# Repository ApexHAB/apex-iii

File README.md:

# Apex III
## A next generation high altitude balloon project by Sutton Grammar School

## Useful links

* [Homepage](http://www.apexhab.org) - http://www.apexhab.org
* [Apex III Homepage](http://www.apexhab.org/apex-iii/) - http://www.apexhab.org/apex-iii/
* [Contact](mailto:team@apexhab.org) - team@apexhab.org
* [Twitter](http://twitter.com/apexhab) - http://twitter.com/apexhab

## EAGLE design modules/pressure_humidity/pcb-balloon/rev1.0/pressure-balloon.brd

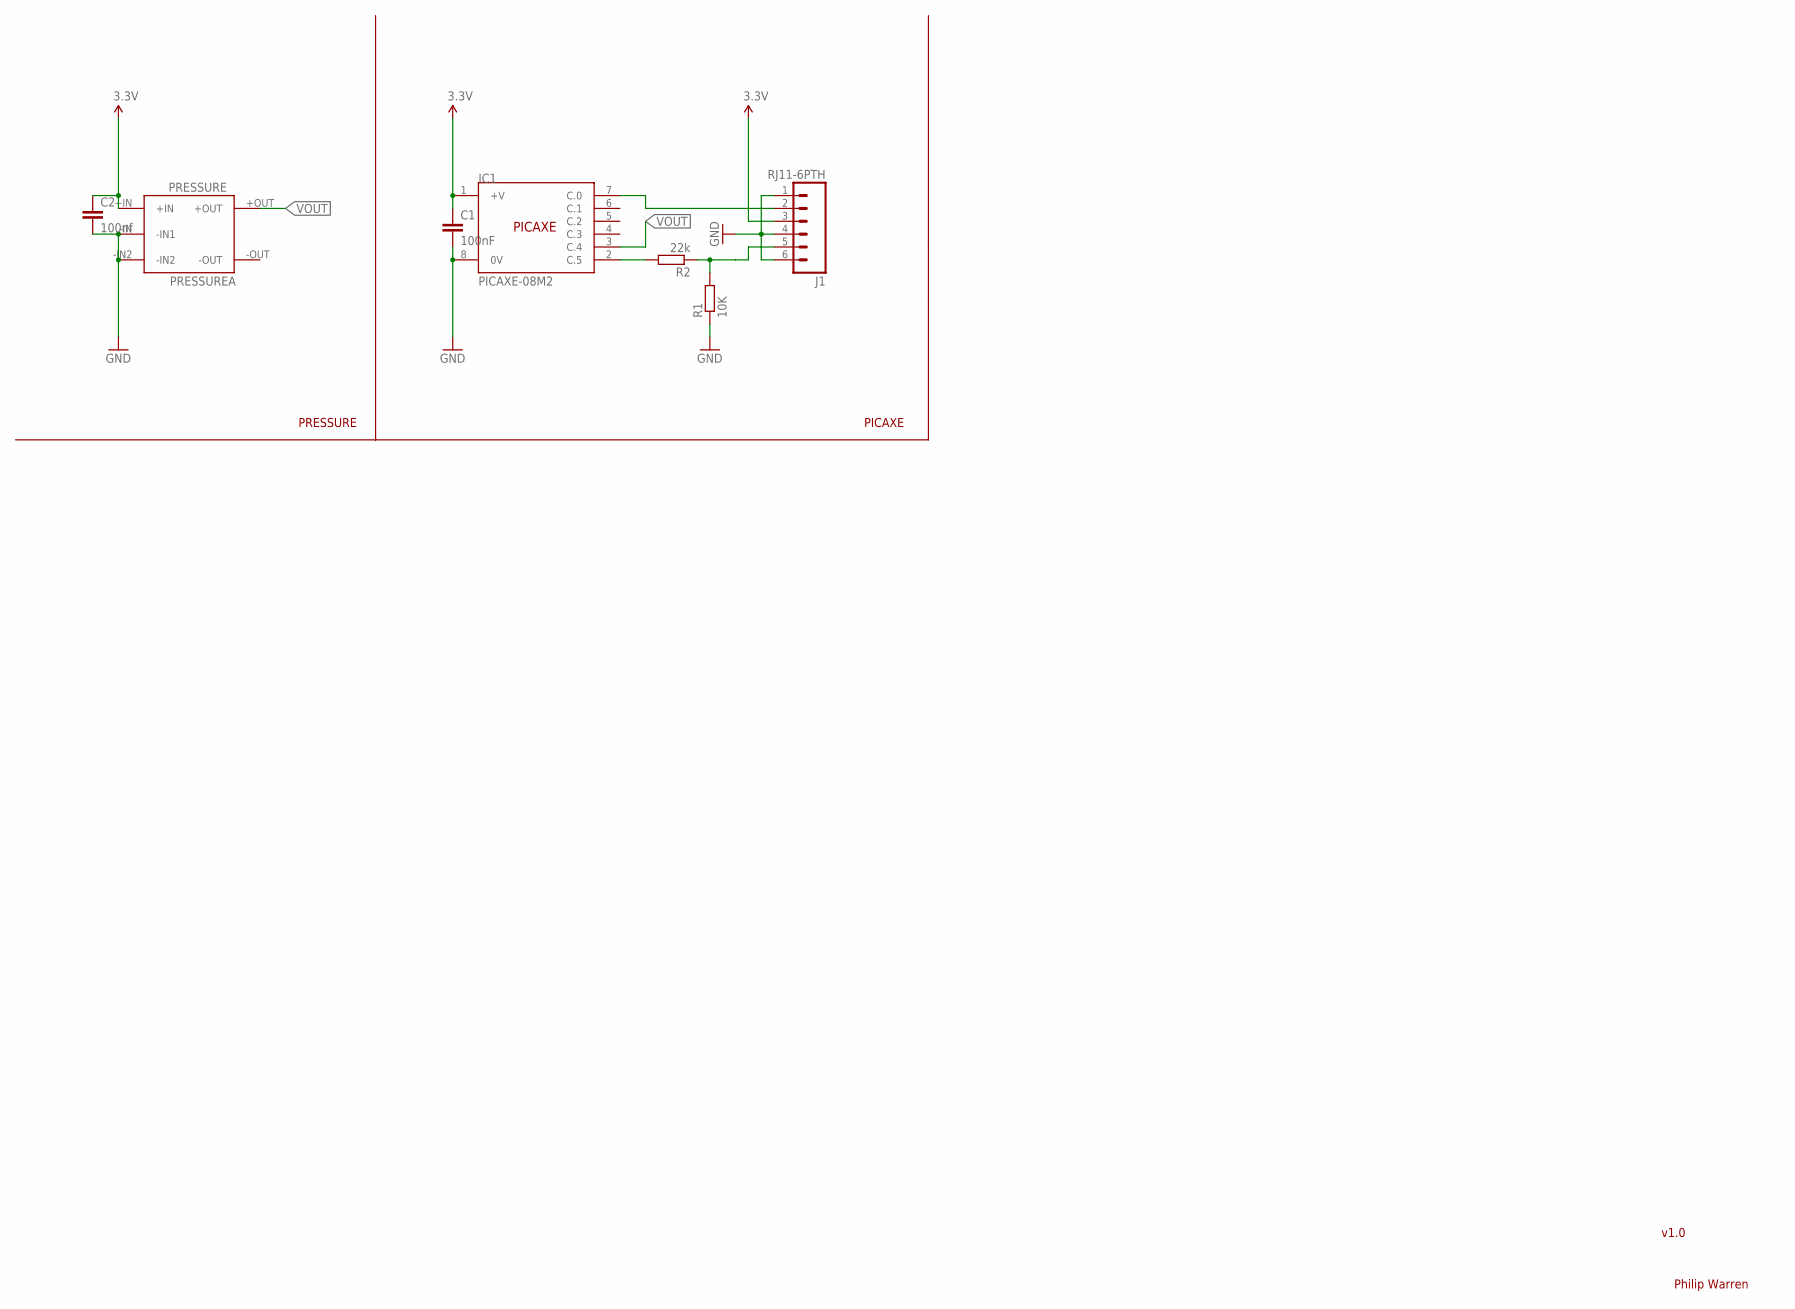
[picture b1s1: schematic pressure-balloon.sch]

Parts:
C1: 100nF; 0805
C2: 100nf; 0805
IC1: PICAXE-08M2; SOIC8
J1: RJ11-6PTH; RJ11-6
PRESSURE: PRESSUREA; PRESSURE
R1: 10K; R0805
R2: 22k; R0805

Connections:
3.3V: C1.1, C2.1, IC1.1 (+V), J1.3, PRESSURE.+IN
GND: C1.2, C2.2, IC1.8 (0V), J1.1, J1.4, J1.6, PRESSURE.-IN (-IN1), PRESSURE.-IN2, R1.1
unnamed: IC1.7 (C.0), J1.2
unnamed: J1.5, R1.2, R2.1
unnamed: IC1.2 (C.5), R2.2
VOUT: IC1.3 (C.4), PRESSURE.+OUT

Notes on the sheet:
PICAXE
PRESSURE
Philip Warren
v1.0

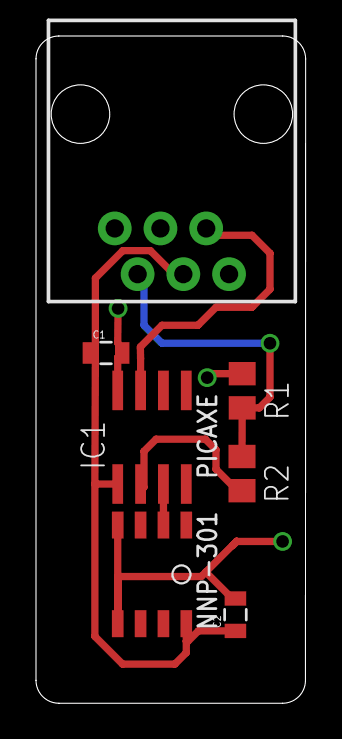
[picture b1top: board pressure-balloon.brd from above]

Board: 2 copper layers, 15.0 x 37.1 mm, 7 parts (0 on the bottom side), 6 nets.

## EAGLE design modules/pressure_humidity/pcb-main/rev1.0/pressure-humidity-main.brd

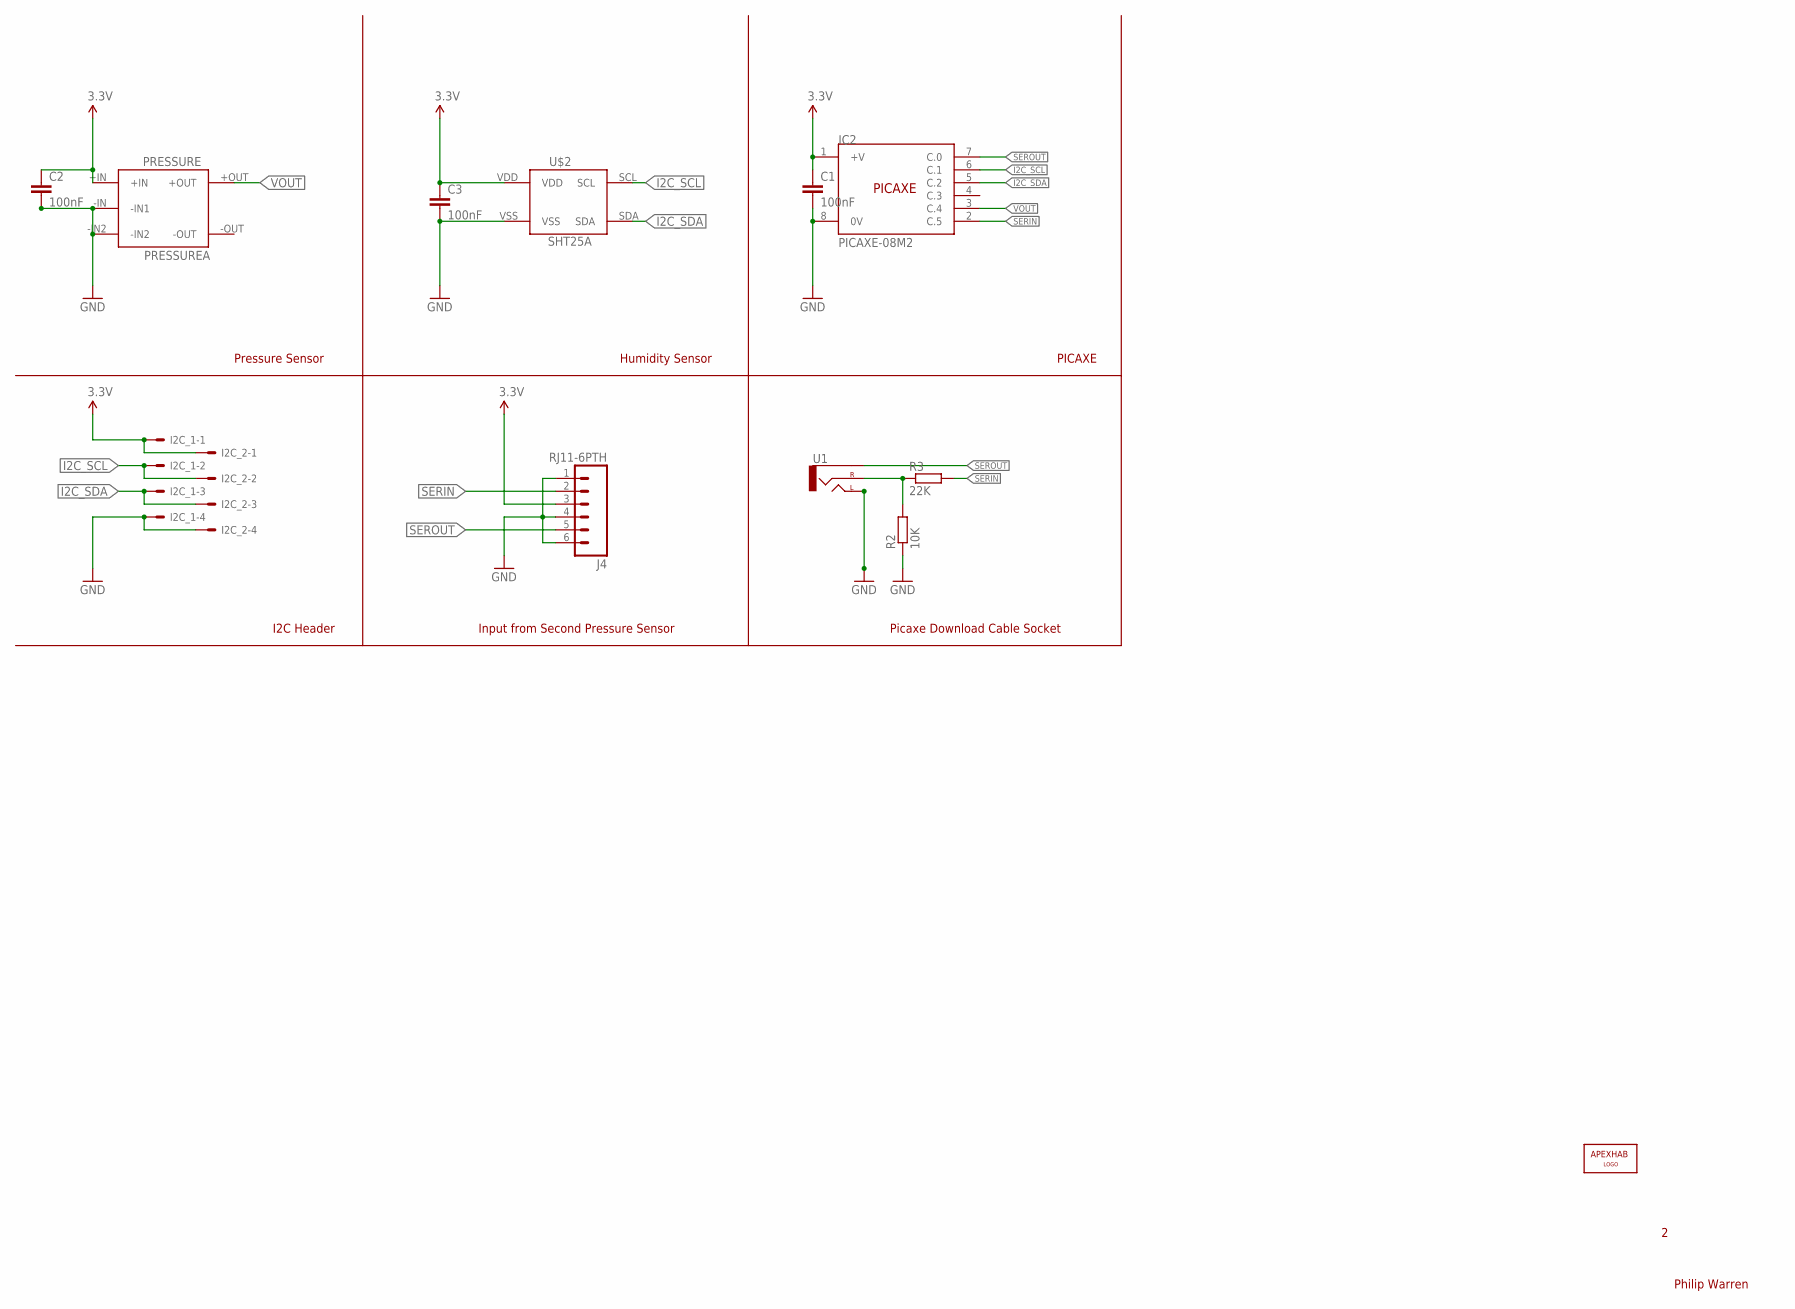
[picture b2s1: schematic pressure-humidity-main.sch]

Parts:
C1, C2, C3: 100nF; 0805
I2C_1, I2C_2: 22-27-2041-04; 6410-04
IC2: PICAXE-08M2; SOIC8
J4: RJ11-6PTH; RJ11-6
JP1: APEXHAB-LOGO_APEXHAB-SMALL; APEXHAB-LOGO-SMALL
PRESSURE: PRESSUREA; PRESSURE
R2: 10K; R0805
R3: 22K; R0805
U1: AUDIO-JACKPTH; AUDIO-JACK
U$2: SHT25A; SHT25

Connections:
3.3V: C1.1, C2.1, C3.1, I2C_1.1, I2C_2.1, IC2.1 (+V), J4.3, PRESSURE.+IN, U$2.VDD
GND: C1.2, C2.2, C3.2, I2C_1.4, I2C_2.4, IC2.8 (0V), J4.1, J4.4, J4.6, PRESSURE.-IN (-IN1), PRESSURE.-IN2, R2.1, U1.TIP (LEFT), U$2.VSS
I2C_SCL: I2C_1.2, I2C_2.2, IC2.6 (C.1), U$2.SCL
I2C_SDA: I2C_1.3, I2C_2.3, IC2.5 (C.2), U$2.SDA
unnamed: R2.2, R3.1, U1.RING (RIGHT)
SERIN: IC2.2 (C.5), J4.2, R3.2
SEROUT: IC2.7 (C.0), J4.5, U1.SLEEVE
VOUT: IC2.3 (C.4), PRESSURE.+OUT

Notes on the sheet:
Pressure Sensor
Humidity Sensor
PICAXE
Picaxe Download Cable Socket
Input from Second Pressure Sensor
I2C Header
Philip Warren

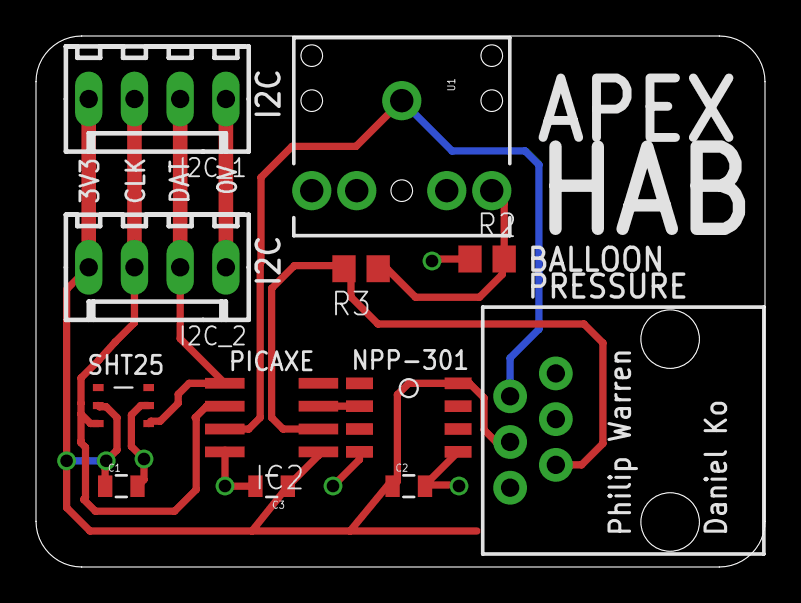
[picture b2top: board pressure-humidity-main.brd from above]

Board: 2 copper layers, 40.5 x 29.5 mm, 13 parts (1 on the bottom side), 8 nets.

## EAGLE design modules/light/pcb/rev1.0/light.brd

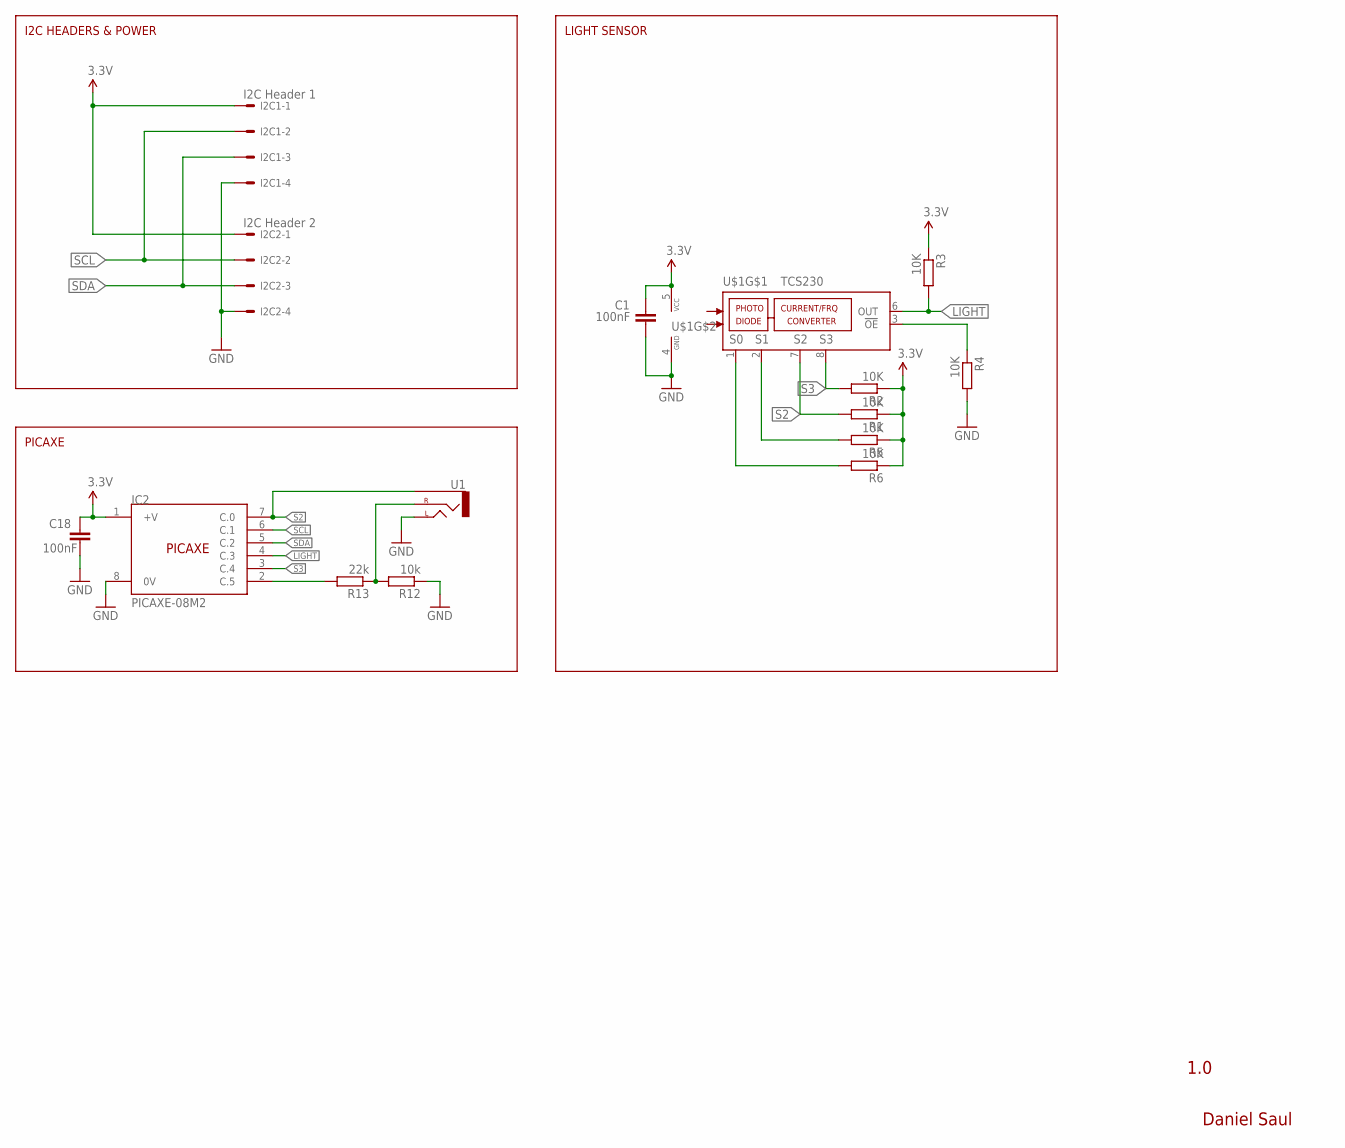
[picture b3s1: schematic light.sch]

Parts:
C1, C18: 100nF; C0805
I2C1: I2C Header 1; 6410-04
I2C2: I2C Header 2; 6410-04
IC2: PICAXE-08M2; SOIC8
R1, R2, R3, R4, R5, R6: 10K; R0805
R12: 10k; R0805
R13: 22k; R0805
U1: AUDIO-JACKPTH; AUDIO-JACK
U$1: TCS230; SOIC8

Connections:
3.3V: C1.1, C18.1, I2C1.1, I2C2.1, IC2.1 (+V), R1.1, R2.1, R3.1, R5.1, R6.1, U$1.5 (VCC)
GND: C1.2, C18.2, I2C1.4, I2C2.4, IC2.8 (0V), R4.2, R12.1, U1.TIP (LEFT), U$1.4 (GND)
LIGHT: IC2.4 (C.3), R3.2, U$1.6 (OUT)
unnamed: R5.2, U$1.2 (S1)
unnamed: R4.1, U$1.3 (!OE)
unnamed: R6.2, U$1.1 (S0)
unnamed: IC2.2 (C.5), R13.2
unnamed: R12.2, R13.1, U1.RING (RIGHT)
S2: IC2.7 (C.0), R1.2, U1.SLEEVE, U$1.7 (S2)
S3: IC2.3 (C.4), R2.2, U$1.8 (S3)
SCL: I2C1.2, I2C2.2, IC2.6 (C.1)
SDA: I2C1.3, I2C2.3, IC2.5 (C.2)

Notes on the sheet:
1.0
Daniel Saul
I2C HEADERS & POWER
PICAXE
LIGHT SENSOR

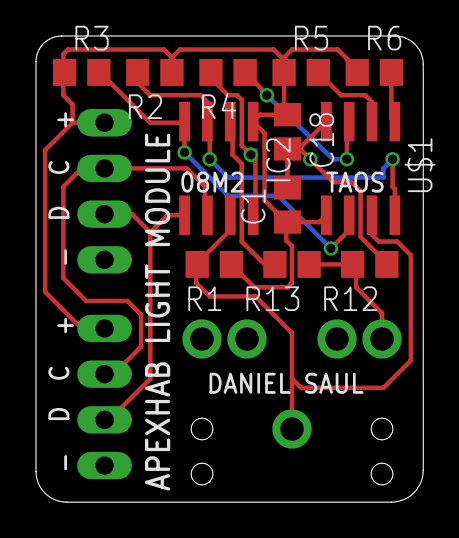
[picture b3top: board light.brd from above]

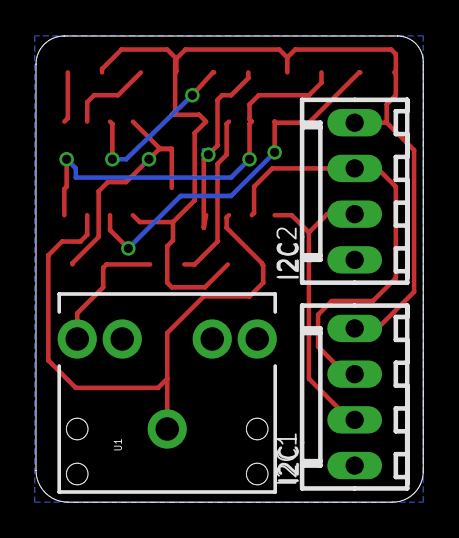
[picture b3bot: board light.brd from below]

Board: 2 copper layers, 21.5 x 25.9 mm, 15 parts (3 on the bottom side), 12 nets.

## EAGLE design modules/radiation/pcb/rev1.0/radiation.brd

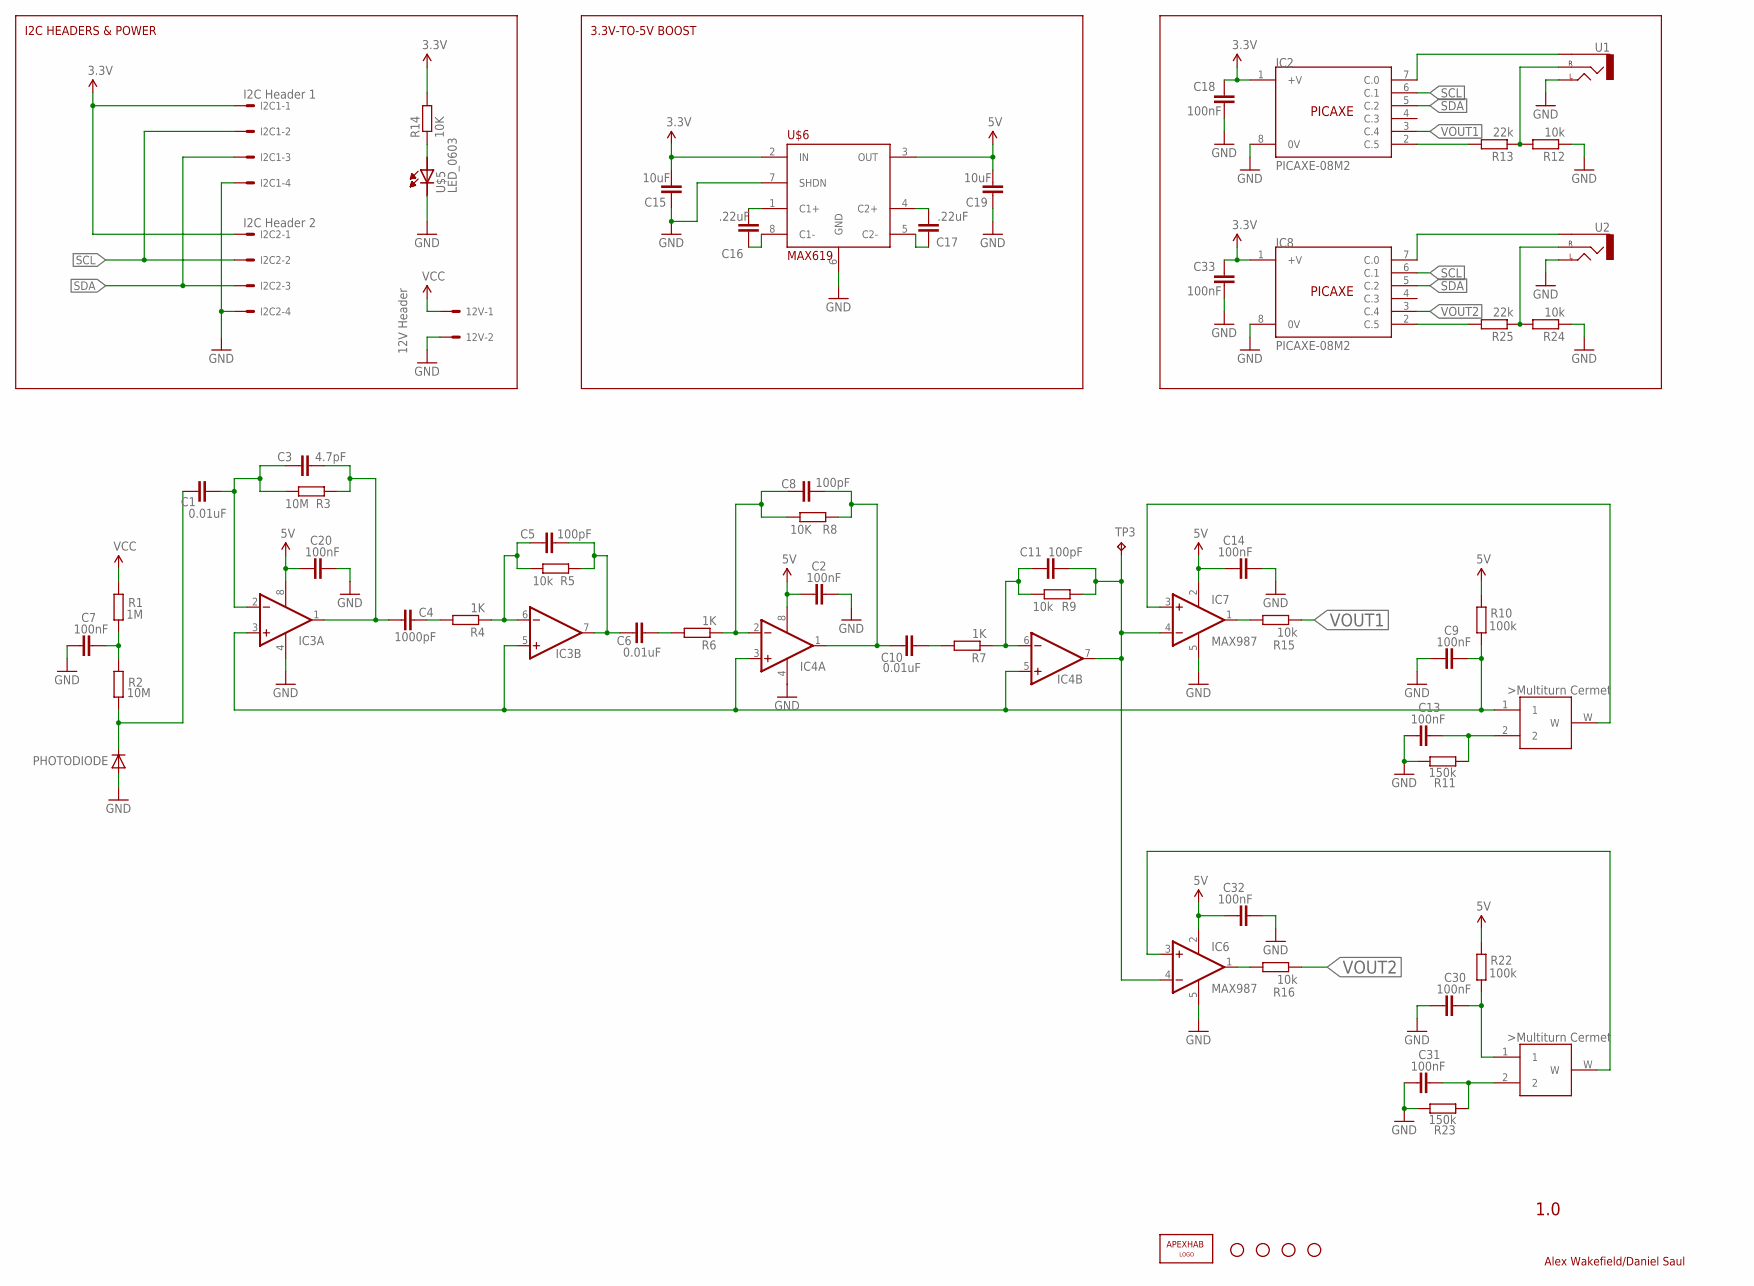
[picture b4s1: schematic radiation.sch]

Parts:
12V: 12V Header; 6410-02
C1, C6, C10: 0.01uF; C0805
C2, C7, C9, C13, C14, C18, C20, C30, C31, C32, C33: 100nF; C0805
C3: 4.7pF; C0805
C4: 1000pF; C0805
C5, C8, C11: 100pF; C0805
C15, C19: 10uF; C0805
C16, C17: .22uF; C0805
I2C1: I2C Header 1; 6410-04
I2C2: I2C Header 2; 6410-04
IC2, IC8: PICAXE-08M2; SOIC8
IC3: max4477; SO08
IC4: <AX4477; SO08
IC6, IC7: MAX987; SOT23-5
JP1: APEXHAB-LOGO_APEX; APEX-LOGO
JP2, JP3, JP4, JP5: STAND-OFF
PHOTODIODE: DIODE-D-2.5; D-2.5
R1: 1M; R0805
R2, R3: 10M; R0805
R4, R6, R7: 1K; R0805
R5, R9, R12, R15, R16, R24: 10k; R0805
R8, R14: 10K; R0805
R10, R22: 100k; R0805
R11, R23: 150k; R0805
R13, R25: 22k; R0805
TP3: TPTP10SQ; TP10SQ
U1, U2: AUDIO-JACKPTH; AUDIO-JACK
U$3, U$4: YL_SMT_11-TURN_CERMET_TRIMMER,_10K_0.25W
U$5: LED_0603; CHIPLED_0603
U$6: MAX619; SO8

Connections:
3.3V: C15.2, C18.1, C33.1, I2C1.1, I2C2.1, IC2.1 (+V), IC8.1 (+V), R14.2, U$6.2 (IN)
5V: C2.1, C14.1, C19.2, C20.1, C32.1, IC3.8 (V+), IC4.8 (V+), IC6.2 (V+), IC7.2 (V+), R10.1, R22.1, U$6.3 (OUT)
GND: 12V.2, C2.2, C7.1, C9.1, C13.1, C14.2, C15.1, C18.2, C19.1, C20.2, C30.1, C31.1, C32.2, C33.2, I2C1.4, I2C2.4, IC2.8 (0V), IC3.4 (V-), IC4.4 (V-), IC6.5 (V-), IC7.5 (V-), IC8.8 (0V), PHOTODIODE.A, R11.2, R12.1, R23.2, R24.1, U1.TIP (LEFT), U2.TIP (LEFT), U$5.C, U$6.6 (GND), U$6.7 (SHDN)
unnamed: C7.2, R1.1, R2.2
unnamed: C1.1, PHOTODIODE.C, R2.1
unnamed: C1.2, C3.1, IC3.2 (-IN), R3.2
unnamed: C4.2, R4.2
unnamed: C3.2, C4.1, IC3.1 (OUT), R3.1
unnamed: C5.1, IC3.6 (-IN), R4.1, R5.2
unnamed: C6.2, R6.2
unnamed: C5.2, C6.1, IC3.7 (OUT), R5.1
unnamed: C8.1, IC4.2 (-IN), R6.1, R8.2
unnamed: C13.2, R11.1, U$4.2
unnamed: C10.2, R7.2
unnamed: C11.1, IC4.6 (-IN), R7.1, R9.2
unnamed: IC8.7 (C.0), U2.SLEEVE
unnamed: IC7.3 (+IN), U$4.W
unnamed: C30.2, R22.2, U$3.1
unnamed: IC7.1 (OUT), R15.2
unnamed: IC2.2 (C.5), R13.2
unnamed: IC2.7 (C.0), U1.SLEEVE
unnamed: IC8.2 (C.5), R25.2
unnamed: R12.2, R13.1, U1.RING (RIGHT)
unnamed: R14.1, U$5.A
unnamed: C16.2, U$6.1 (C1+)
unnamed: C16.1, U$6.8 (C1-)
unnamed: C17.2, U$6.4 (C2+)
unnamed: C17.1, U$6.5 (C2-)
unnamed: C11.2, IC4.7 (OUT), IC6.4 (-IN), IC7.4 (-IN), R9.1, TP3.TP
unnamed: IC6.1 (OUT), R16.2
unnamed: C8.2, C10.1, IC4.1 (OUT), R8.1
unnamed: C9.2, IC3.3 (+IN), IC3.5 (+IN), IC4.3 (+IN), IC4.5 (+IN), R10.2, U$4.1
unnamed: C31.2, R23.1, U$3.2
unnamed: IC6.3 (+IN), U$3.W
unnamed: R24.2, R25.1, U2.RING (RIGHT)
SCL: I2C1.2, I2C2.2, IC2.6 (C.1), IC8.6 (C.1)
SDA: I2C1.3, I2C2.3, IC2.5 (C.2), IC8.5 (C.2)
VCC: 12V.1, R1.2
VOUT1: IC2.3 (C.4), R15.1
VOUT2: IC8.3 (C.4), R16.1

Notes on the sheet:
1.0
Alex Wakefield/Daniel Saul
I2C HEADERS & POWER
3.3V-TO-5V BOOST

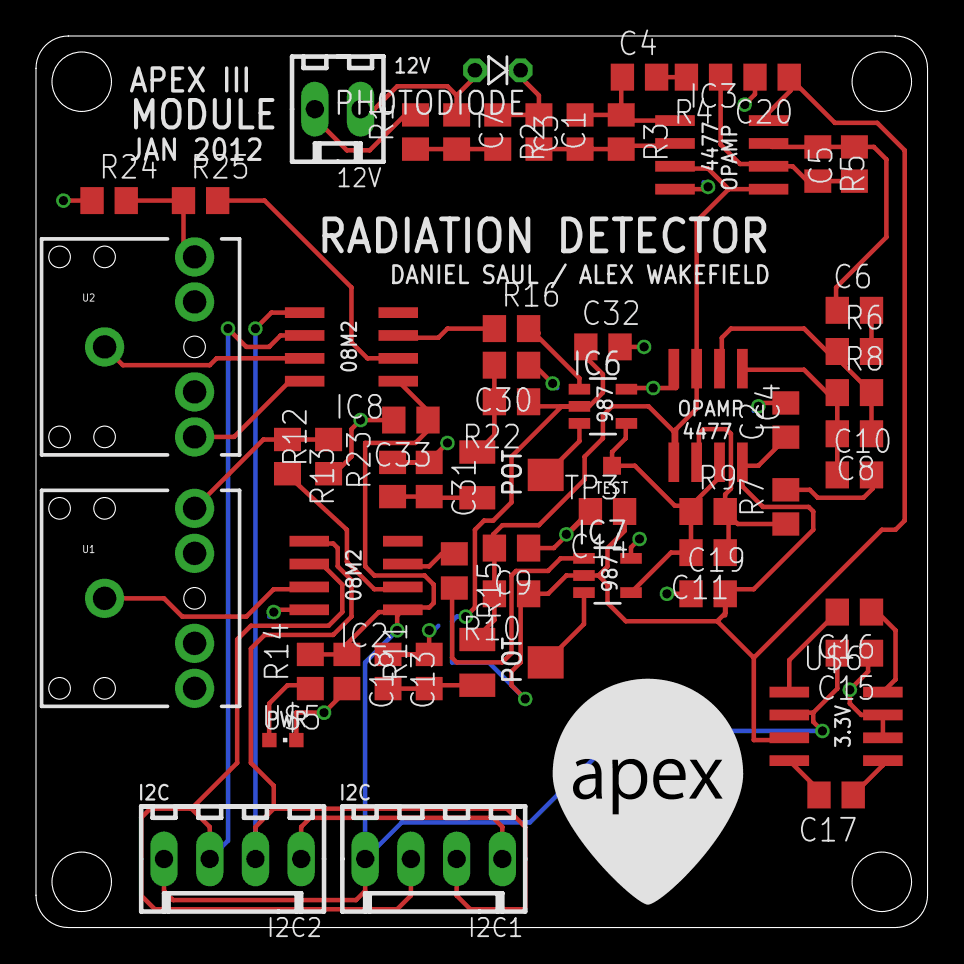
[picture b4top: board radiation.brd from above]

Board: 2 copper layers, 49.5 x 49.5 mm, 65 parts (0 on the bottom side), 40 nets.

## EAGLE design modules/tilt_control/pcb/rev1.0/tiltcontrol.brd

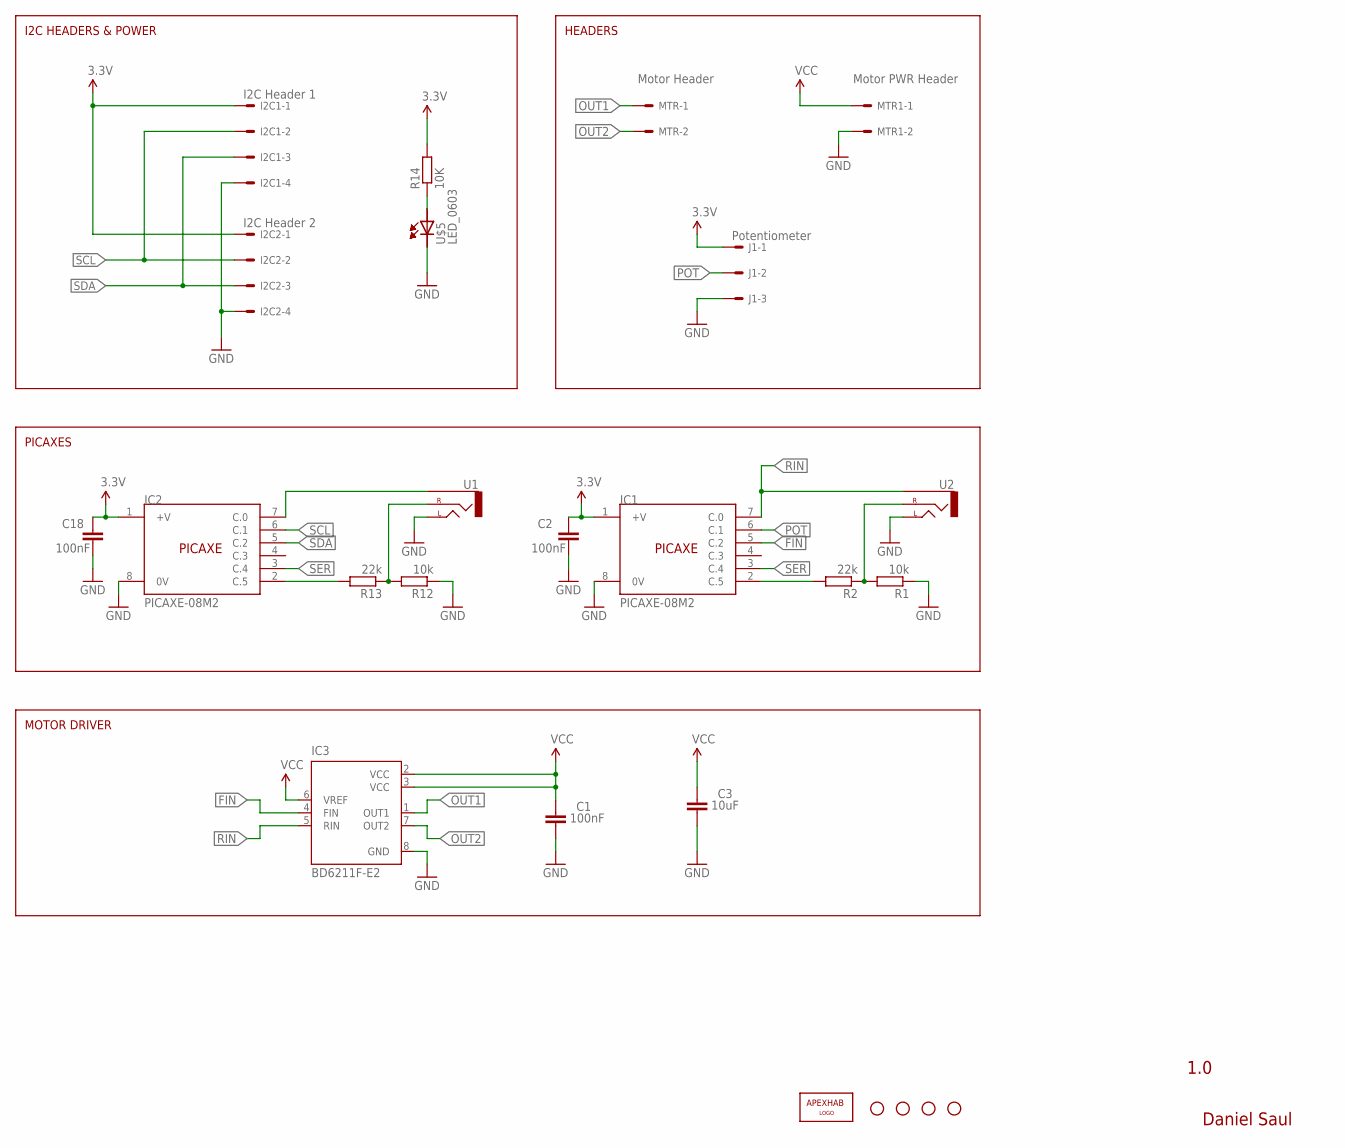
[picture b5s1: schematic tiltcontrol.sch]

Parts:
C1, C2, C18: 100nF; C0805
C3: 10uF; C0805
I2C1: I2C Header 1; 6410-04
I2C2: I2C Header 2; 6410-04
IC1, IC2: PICAXE-08M2; SOIC8
IC3: BD6211F-E2; SOP8
J1: Potentiometer; 6410-03
JP1: APEXHAB-LOGO_APEXHAB-SMALL; APEXHAB-LOGO-SMALL
JP2, JP3, JP4, JP5: STAND-OFF
MTR: Motor Header; 6410-02
MTR1: Motor PWR Header; 6410-02
R1, R12: 10k; R0805
R2, R13: 22k; R0805
R14: 10K; R0805
U1, U2: AUDIO-JACKPTH; AUDIO-JACK
U$5: LED_0603; CHIPLED_0603

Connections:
3.3V: C2.1, C18.1, I2C1.1, I2C2.1, IC1.1 (+V), IC2.1 (+V), J1.1, R14.2
FIN: IC1.5 (C.2), IC3.4 (FIN)
GND: C1.2, C2.2, C3.2, C18.2, I2C1.4, I2C2.4, IC1.8 (0V), IC2.8 (0V), IC3.8 (GND), J1.3, MTR1.2, R1.1, R12.1, U1.TIP (LEFT), U2.TIP (LEFT), U$5.C
unnamed: IC1.2 (C.5), R2.2
unnamed: R1.2, R2.1, U2.RING (RIGHT)
unnamed: IC2.2 (C.5), R13.2
unnamed: IC2.7 (C.0), U1.SLEEVE
unnamed: R12.2, R13.1, U1.RING (RIGHT)
unnamed: R14.1, U$5.A
OUT1: IC3.1 (OUT1), MTR.1
OUT2: IC3.7 (OUT2), MTR.2
POT: IC1.6 (C.1), J1.2
RIN: IC1.7 (C.0), IC3.5 (RIN), U2.SLEEVE
SCL: I2C1.2, I2C2.2, IC2.6 (C.1)
SDA: I2C1.3, I2C2.3, IC2.5 (C.2)
SER: IC1.3 (C.4), IC2.3 (C.4)
VCC: C1.1, C3.1, IC3.2 (VCC), IC3.3 (VCC), IC3.6 (VREF), MTR1.1

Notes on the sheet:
1.0
Daniel Saul
I2C HEADERS & POWER
HEADERS
PICAXES
MOTOR DRIVER

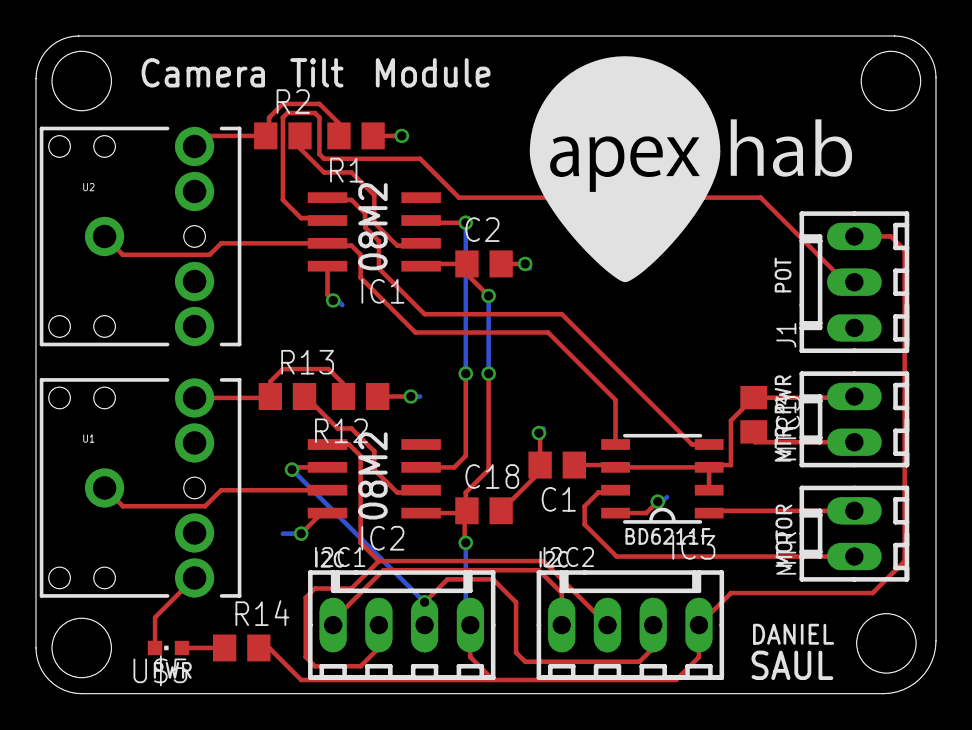
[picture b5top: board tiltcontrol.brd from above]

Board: 2 copper layers, 50.0 x 36.5 mm, 25 parts (0 on the bottom side), 17 nets.

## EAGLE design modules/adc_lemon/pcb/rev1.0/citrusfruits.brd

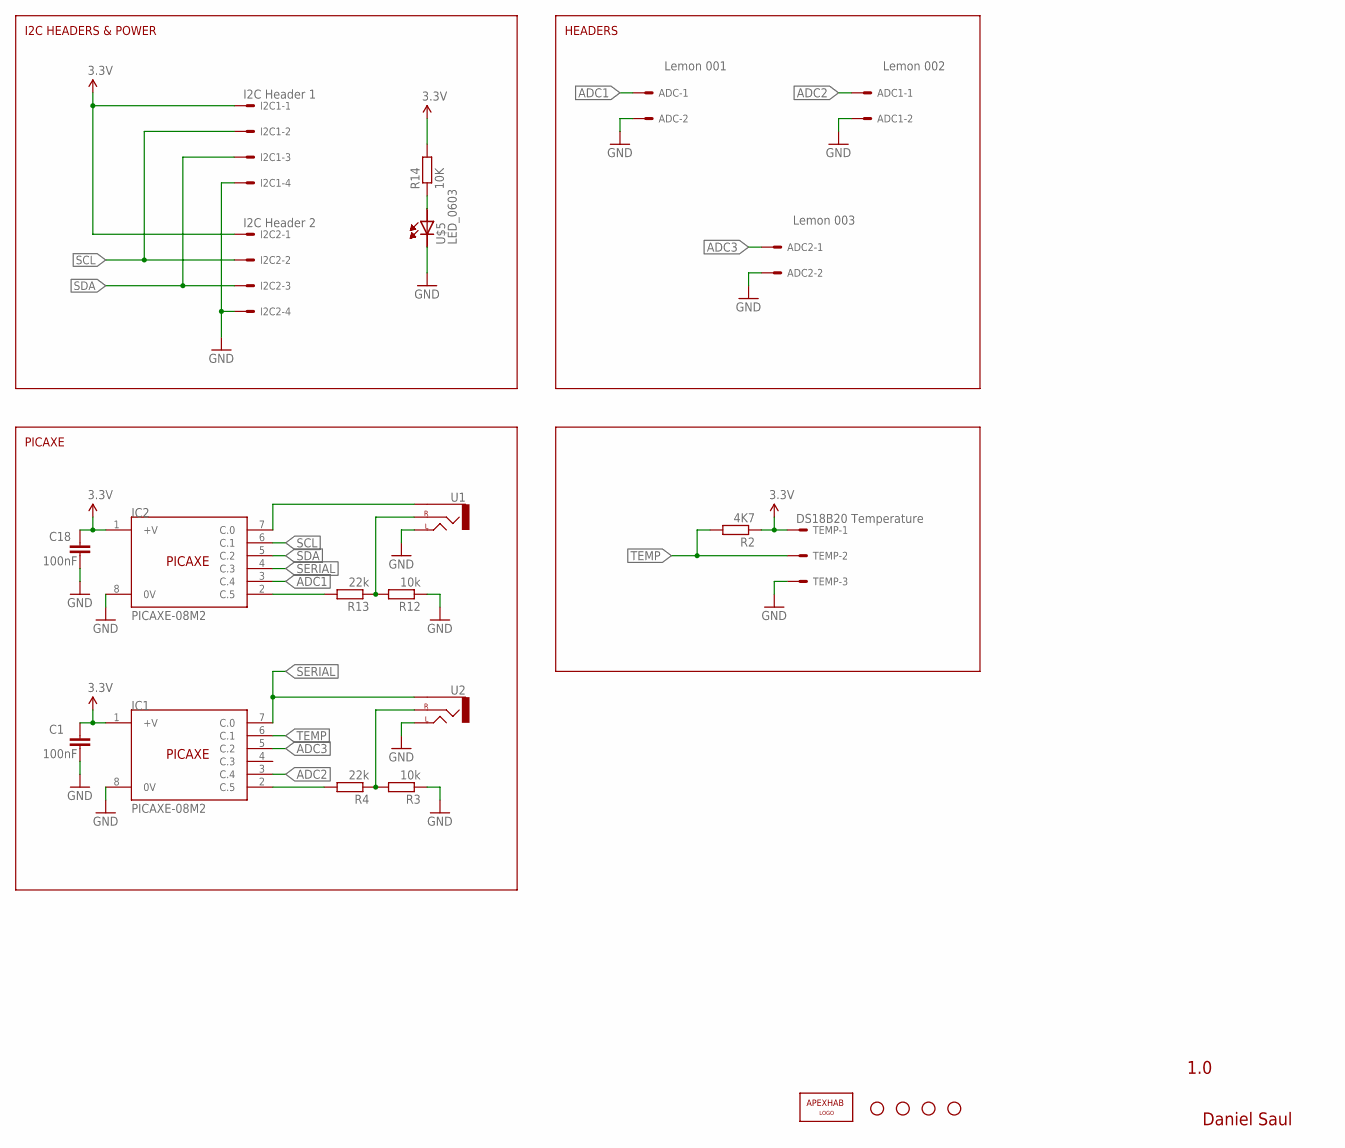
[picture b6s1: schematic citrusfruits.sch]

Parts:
ADC: Lemon 001; 6410-02
ADC1: Lemon 002; 6410-02
ADC2: Lemon 003; 6410-02
C1, C18: 100nF; C0805
I2C1: I2C Header 1; 6410-04
I2C2: I2C Header 2; 6410-04
IC1, IC2: PICAXE-08M2; SOIC8
JP1: APEXHAB-LOGO_APEXHAB-SMALL; APEXHAB-LOGO-SMALL
JP2, JP3, JP4, JP5: STAND-OFF
R2: 4K7; R0805
R3, R12: 10k; R0805
R4, R13: 22k; R0805
R14: 10K; R0805
TEMP: DS18B20 Temperature; 6410-03
U1, U2: AUDIO-JACKPTH; AUDIO-JACK
U$5: LED_0603; CHIPLED_0603

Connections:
3.3V: C1.1, C18.1, I2C1.1, I2C2.1, IC1.1 (+V), IC2.1 (+V), R2.1, R14.2, TEMP.1
ADC1: ADC.1, IC2.3 (C.4)
ADC2: ADC1.1, IC1.3 (C.4)
ADC3: ADC2.1, IC1.5 (C.2)
GND: ADC.2, ADC1.2, ADC2.2, C1.2, C18.2, I2C1.4, I2C2.4, IC1.8 (0V), IC2.8 (0V), R3.1, R12.1, TEMP.3, U1.TIP (LEFT), U2.TIP (LEFT), U$5.C
unnamed: IC1.2 (C.5), R4.2
unnamed: R3.2, R4.1, U2.RING (RIGHT)
unnamed: IC2.2 (C.5), R13.2
unnamed: IC2.7 (C.0), U1.SLEEVE
unnamed: R12.2, R13.1, U1.RING (RIGHT)
unnamed: R14.1, U$5.A
SCL: I2C1.2, I2C2.2, IC2.6 (C.1)
SDA: I2C1.3, I2C2.3, IC2.5 (C.2)
SERIAL: IC1.7 (C.0), IC2.4 (C.3), U2.SLEEVE
TEMP: IC1.6 (C.1), R2.2, TEMP.2

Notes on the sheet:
1.0
Daniel Saul
I2C HEADERS & POWER
HEADERS
PICAXE

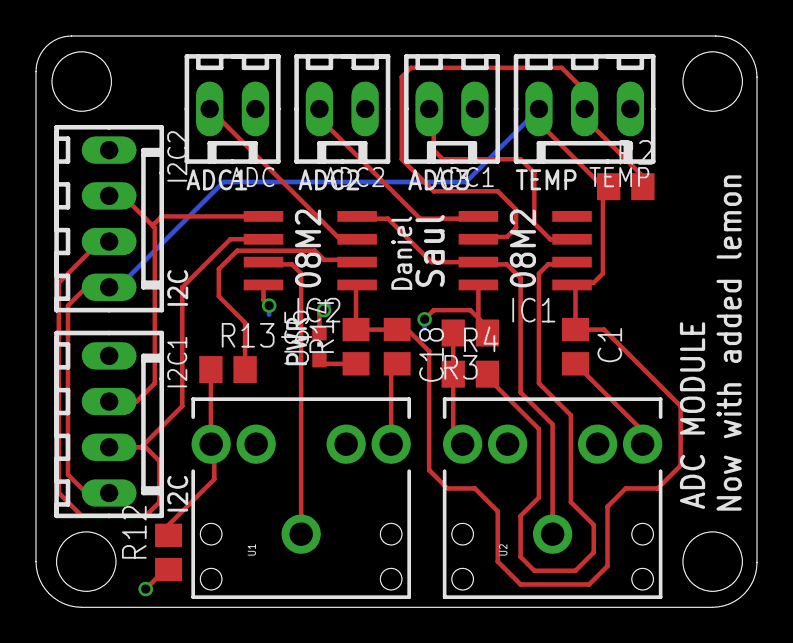
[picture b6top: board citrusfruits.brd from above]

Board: 2 copper layers, 40.1 x 31.7 mm, 24 parts (1 on the bottom side), 15 nets.

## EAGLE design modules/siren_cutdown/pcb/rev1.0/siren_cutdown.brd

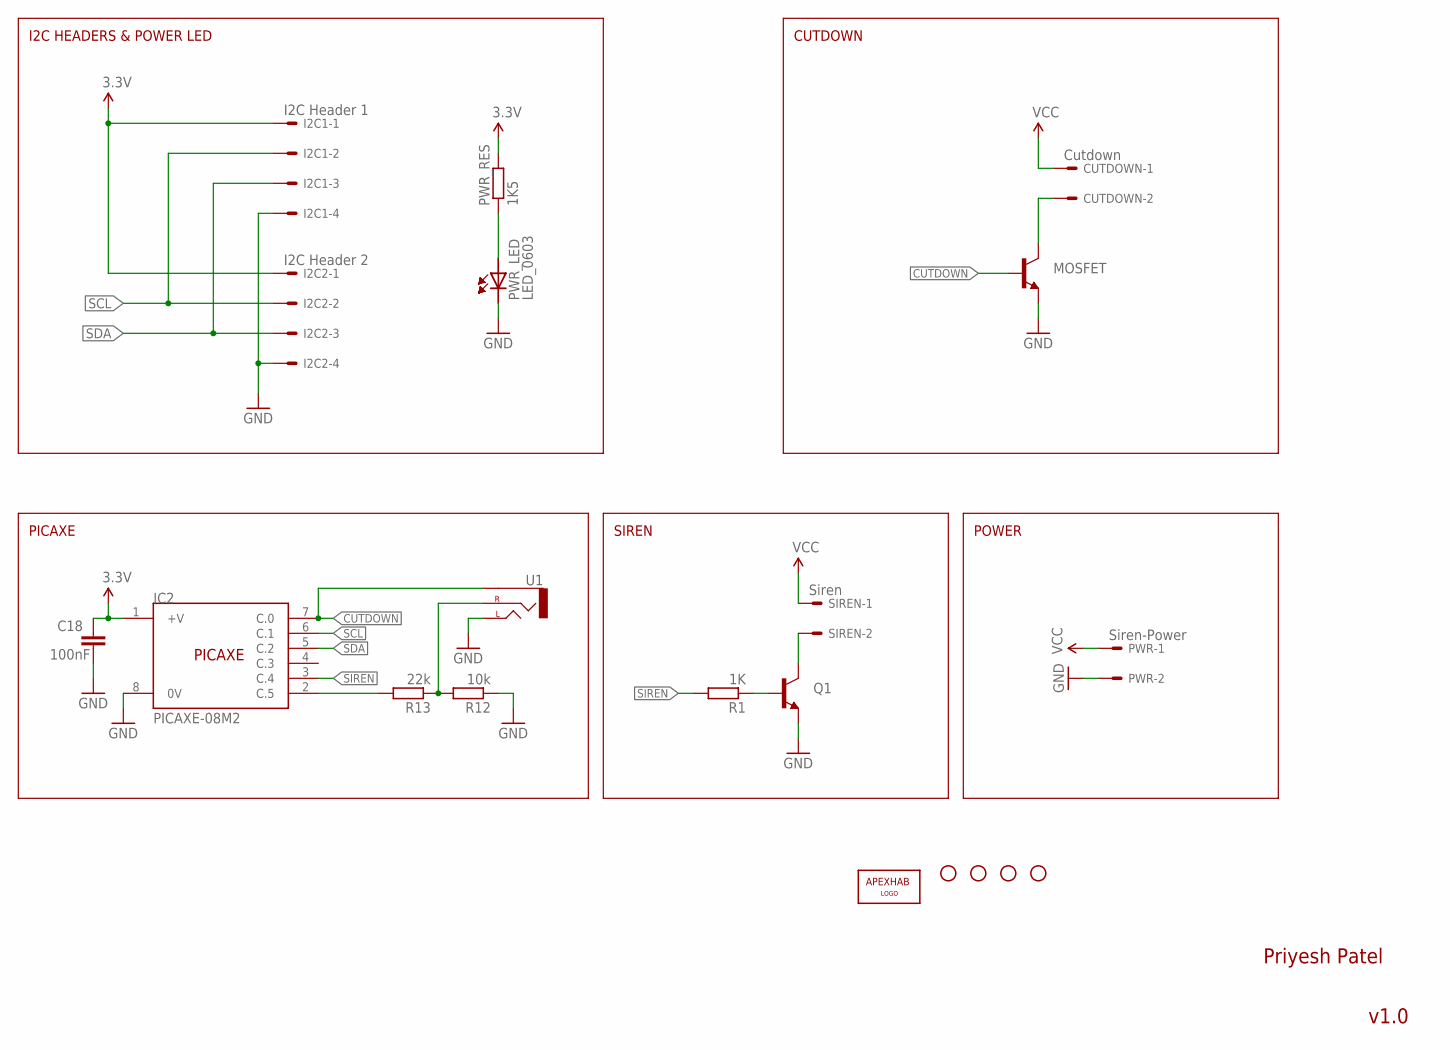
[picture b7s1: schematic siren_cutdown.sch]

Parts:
C18: 100nF; C0805
CUTDOWN: Cutdown; 6410-02
I2C1: I2C Header 1; 6410-04
I2C2: I2C Header 2; 6410-04
IC2: PICAXE-08M2; SOIC8
JP1: APEXHAB-LOGO_APEXHAB-SMALL; APEXHAB-LOGO-SMALL
JP2, JP3, JP4, JP5: STAND-OFF
MOSFET: TRANSISTOR_NPNSOT23; SOT23
PWR: Siren-Power; 6410-02
PWR_LED: LED_0603; CHIPLED_0603
PWR_RES: 1K5; R0805
Q1: TRANSISTOR_NPN"; SOT223
R1: 1K; R0805
R12: 10k; R0805
R13: 22k; R0805
SIREN: Siren; 6410-02
U1: AUDIO-JACKPTH; AUDIO-JACK

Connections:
3.3V: C18.1, I2C1.1, I2C2.1, IC2.1 (+V), PWR_RES.2
CUTDOWN: IC2.7 (C.0), MOSFET.1 (B), U1.SLEEVE
GND: C18.2, I2C1.4, I2C2.4, IC2.8 (0V), MOSFET.2 (E), PWR.2, PWR_LED.C, Q1.3 (E), R12.1, U1.TIP (LEFT)
unnamed: Q1.1 (B), R1.1
unnamed: Q1.2 (C), SIREN.2
unnamed: CUTDOWN.2, MOSFET.3 (C)
unnamed: IC2.2 (C.5), R13.2
unnamed: R12.2, R13.1, U1.RING (RIGHT)
unnamed: PWR_LED.A, PWR_RES.1
SCL: I2C1.2, I2C2.2, IC2.6 (C.1)
SDA: I2C1.3, I2C2.3, IC2.5 (C.2)
SIREN: IC2.3 (C.4), R1.2
VCC: CUTDOWN.1, PWR.1, SIREN.1

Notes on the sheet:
Priyesh Patel
v1.0
I2C HEADERS & POWER LED
PICAXE
SIREN
POWER
CUTDOWN

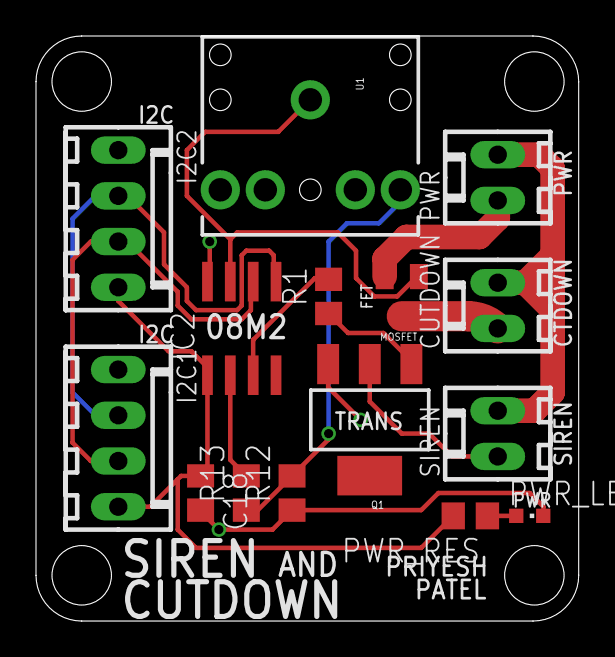
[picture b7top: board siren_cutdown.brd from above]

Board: 2 copper layers, 30.1 x 32.5 mm, 20 parts (1 on the bottom side), 13 nets.

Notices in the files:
parts and their libraries:
SparkFun: Licensing: CC v3.0 Share-Alike You are welcome to use this library for commercial purposes.
